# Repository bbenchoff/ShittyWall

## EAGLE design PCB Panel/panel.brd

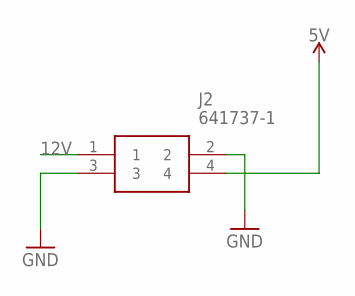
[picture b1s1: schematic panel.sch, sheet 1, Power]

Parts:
J2: 641737-1

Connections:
5V: J2.4; also elsewhere on the board
12V: J2.1
GND: J2.2, J2.3; also elsewhere on the board

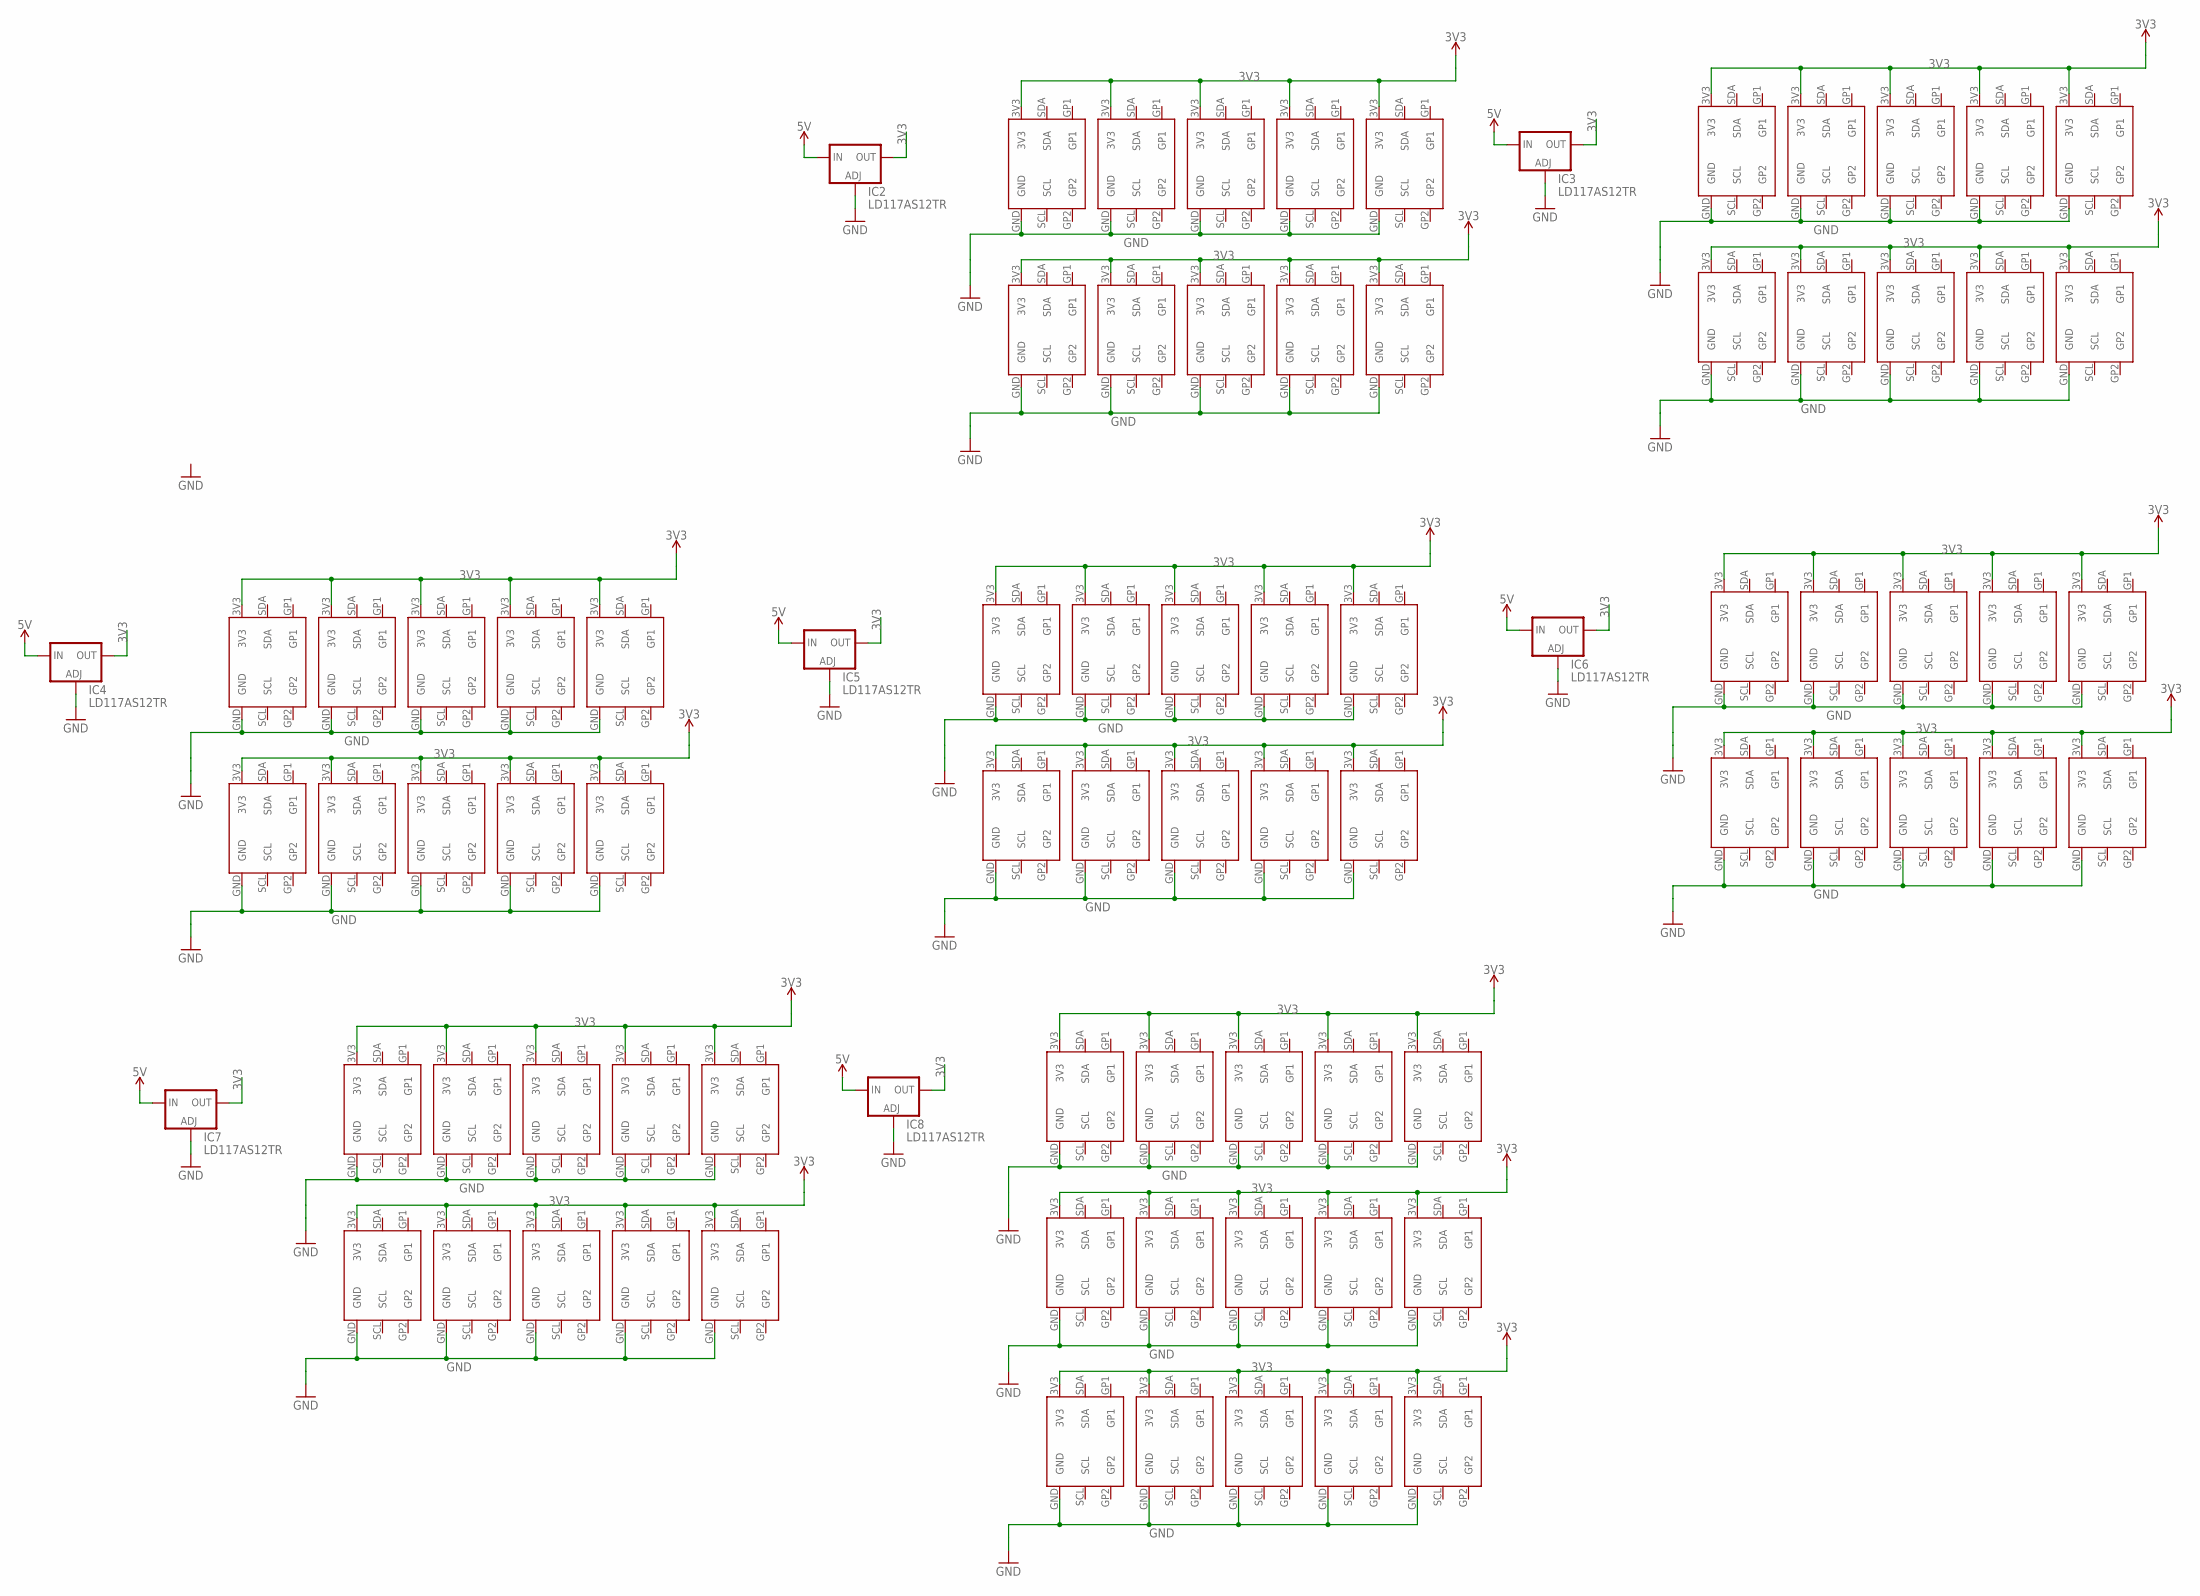
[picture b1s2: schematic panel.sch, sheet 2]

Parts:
IC2, IC3, IC4, IC5, IC6, IC7, IC8: LD117AS12TR; SOT223
U$11, U$12, U$13, U$14, U$15, U$16, U$17, U$18, U$19, U$20, U$21, U$22, U$23, U$24, U$25, U$26, U$27, U$28, U$29, U$30, U$31, U$32, U$33, U$34, U$35, U$36, U$37, U$38, U$39, U$40, U$41, U$42, U$43, U$44, U$45, U$46, U$47, U$48, U$49, U$50, U$51, U$52, U$53, U$54, U$55, U$56, U$57, U$58, U$59, U$60, U$61, U$62, U$63, U$64, U$65, U$66, U$67, U$68, U$69, U$70, U$71, U$72, U$73, U$74, U$75, U$76, U$77, U$78, U$79, U$80, U$81, U$82, U$83, U$84, U$85: SAO1.69BIS; 2X3

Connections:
3V3: IC2.4 (OUT), IC3.4 (OUT), IC4.4 (OUT), IC5.4 (OUT), IC6.4 (OUT), IC7.4 (OUT), IC8.4 (OUT), U$11.3V3, U$12.3V3, U$13.3V3, U$14.3V3, U$15.3V3, U$16.3V3, U$17.3V3, U$18.3V3, U$19.3V3, U$20.3V3, U$21.3V3, U$22.3V3, U$23.3V3, U$24.3V3, U$25.3V3, U$26.3V3, U$27.3V3, U$28.3V3, U$29.3V3, U$30.3V3, U$31.3V3, U$32.3V3, U$33.3V3, U$34.3V3, U$35.3V3, U$36.3V3, U$37.3V3, U$38.3V3, U$39.3V3, U$40.3V3, U$41.3V3, U$42.3V3, U$43.3V3, U$44.3V3, U$45.3V3, U$46.3V3, U$47.3V3, U$48.3V3, U$49.3V3, U$50.3V3, U$51.3V3, U$52.3V3, U$53.3V3, U$54.3V3, U$55.3V3, U$56.3V3, U$57.3V3, U$58.3V3, U$59.3V3, U$60.3V3, U$61.3V3, U$62.3V3, U$63.3V3, U$64.3V3, U$65.3V3, U$66.3V3, U$67.3V3, U$68.3V3, U$69.3V3, U$70.3V3, U$71.3V3, U$72.3V3, U$73.3V3, U$74.3V3, U$75.3V3, U$76.3V3, U$77.3V3, U$78.3V3, U$79.3V3, U$80.3V3, U$81.3V3, U$82.3V3, U$83.3V3, U$84.3V3, U$85.3V3
5V: IC2.3 (IN), IC3.3 (IN), IC4.3 (IN), IC5.3 (IN), IC6.3 (IN), IC7.3 (IN), IC8.3 (IN); also elsewhere on the board
GND: IC2.1 (ADJ), IC3.1 (ADJ), IC4.1 (ADJ), IC5.1 (ADJ), IC6.1 (ADJ), IC7.1 (ADJ), IC8.1 (ADJ), U$11.GND, U$12.GND, U$13.GND, U$14.GND, U$15.GND, U$16.GND, U$17.GND, U$18.GND, U$19.GND, U$20.GND, U$21.GND, U$22.GND, U$23.GND, U$24.GND, U$25.GND, U$26.GND, U$27.GND, U$28.GND, U$29.GND, U$30.GND, U$31.GND, U$32.GND, U$33.GND, U$34.GND, U$35.GND, U$36.GND, U$37.GND, U$38.GND, U$39.GND, U$40.GND, U$41.GND, U$42.GND, U$43.GND, U$44.GND, U$45.GND, U$46.GND, U$47.GND, U$48.GND, U$49.GND, U$50.GND, U$51.GND, U$52.GND, U$53.GND, U$54.GND, U$55.GND, U$56.GND, U$57.GND, U$58.GND, U$59.GND, U$60.GND, U$61.GND, U$62.GND, U$63.GND, U$64.GND, U$65.GND, U$66.GND, U$67.GND, U$68.GND, U$69.GND, U$70.GND, U$71.GND, U$72.GND, U$73.GND, U$74.GND, U$75.GND, U$76.GND, U$77.GND, U$78.GND, U$79.GND, U$80.GND, U$81.GND, U$82.GND, U$83.GND, U$84.GND, U$85.GND; also elsewhere on the board

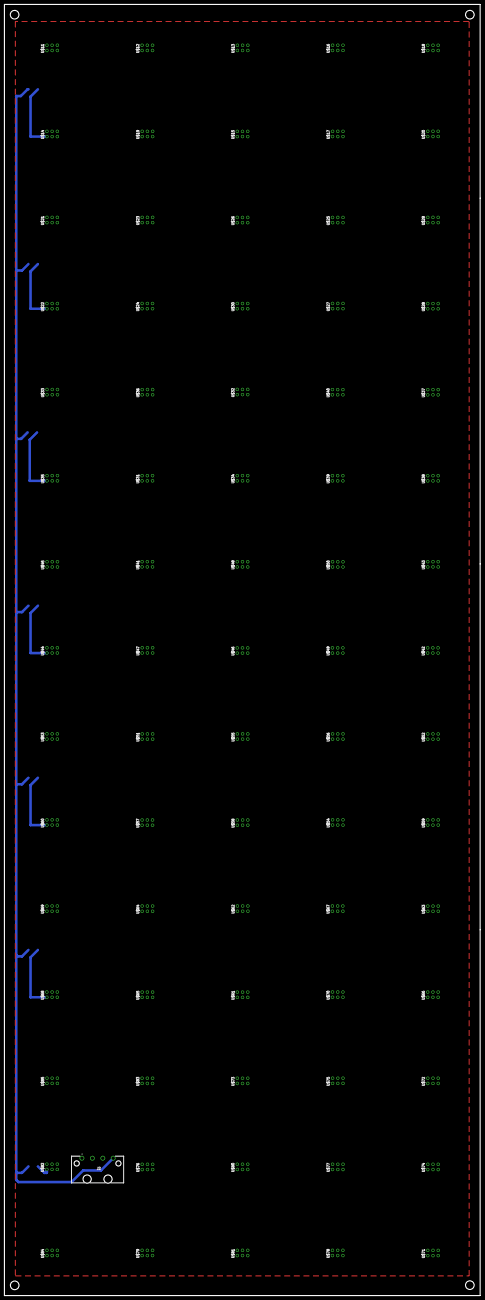
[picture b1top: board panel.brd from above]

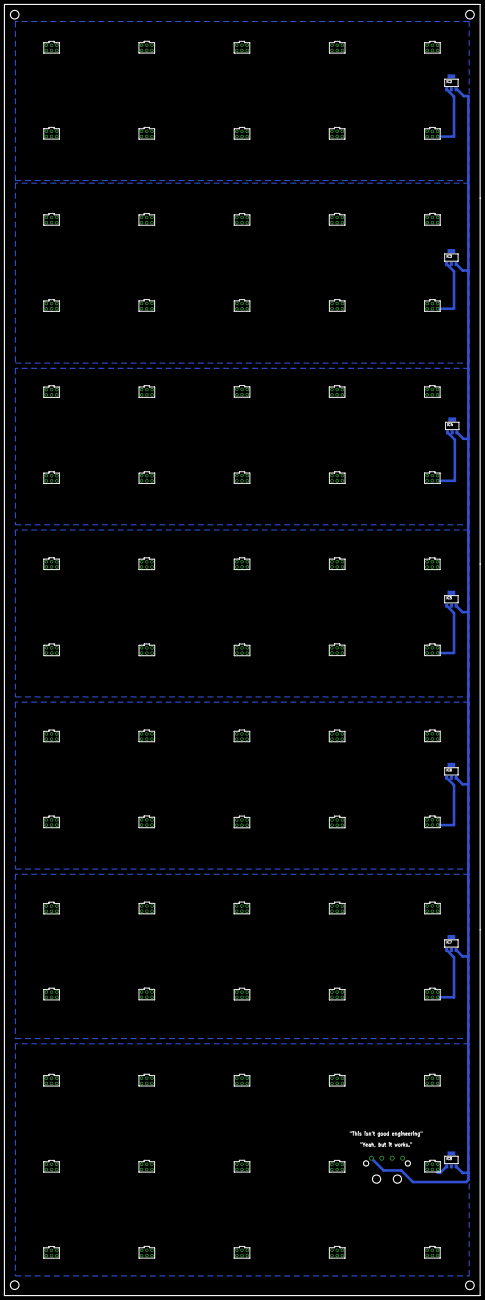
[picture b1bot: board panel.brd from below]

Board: 2 copper layers, 231.7 x 628.8 mm, 83 parts (7 on the bottom side), 3 nets.

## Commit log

2019-10-04 AddedMechanical
2019-10-04 Added PCB panel

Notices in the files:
parts and their libraries:
SparkFun-PowerSymbols: Licensing: Creative Commons ShareAlike 4.0 International - https://creativecommons.org/licenses/by-sa/4.0
